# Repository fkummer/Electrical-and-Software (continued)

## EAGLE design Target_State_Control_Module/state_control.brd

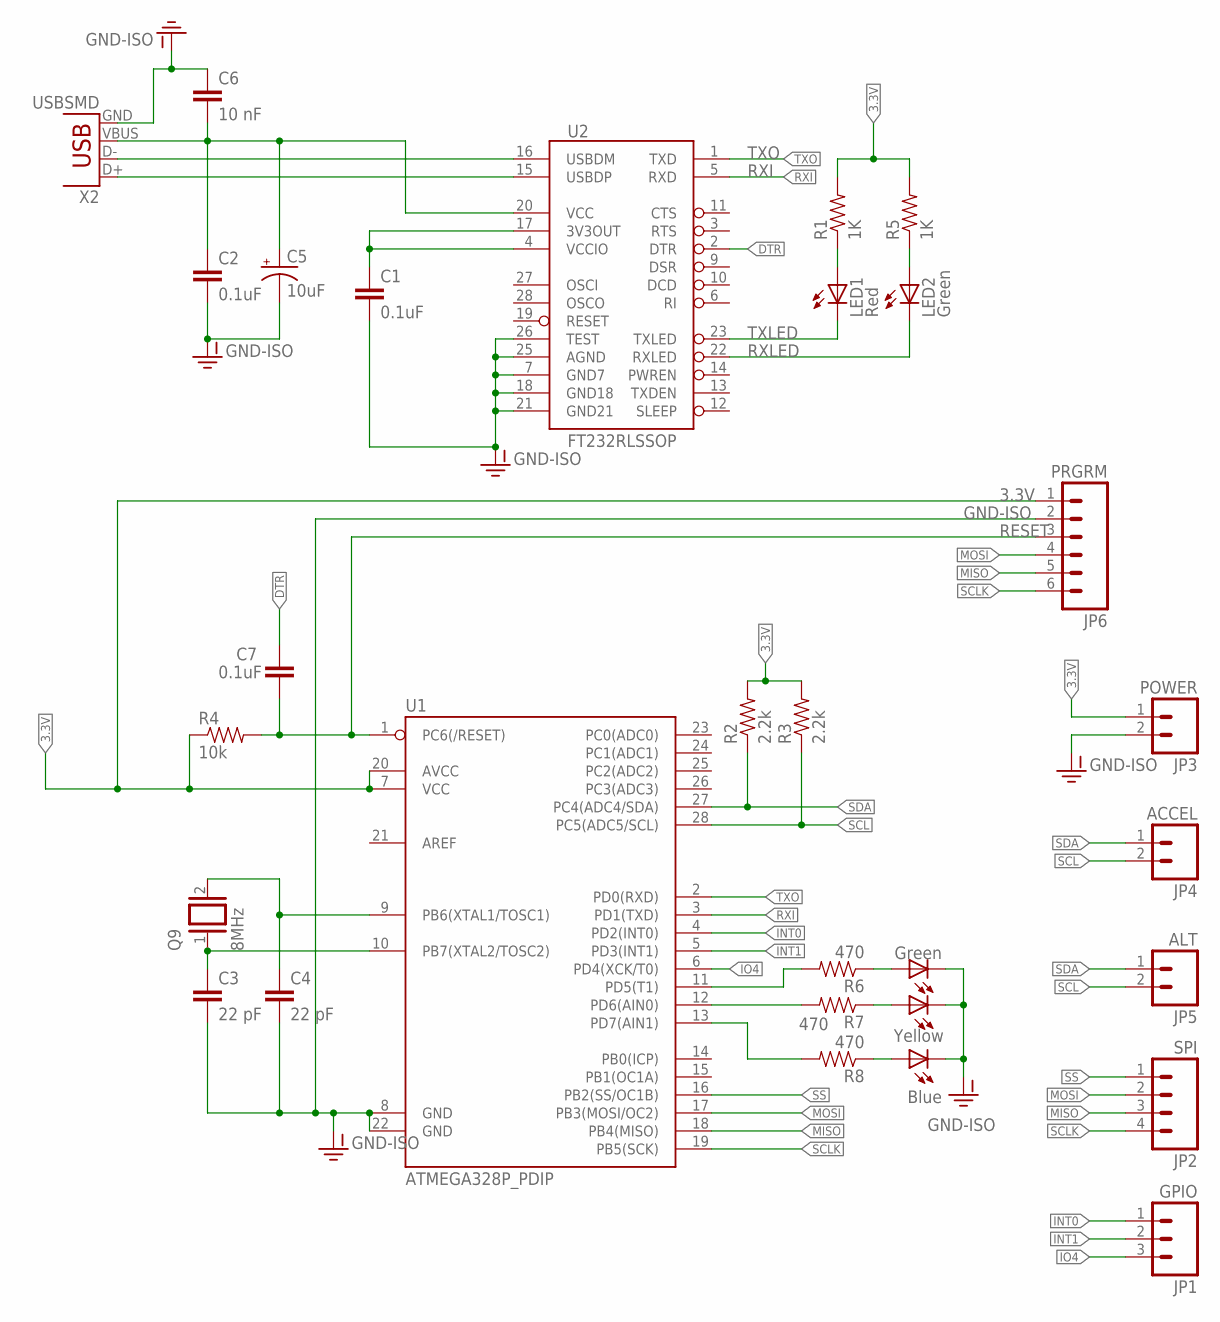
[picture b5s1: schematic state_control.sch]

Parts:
C1, C2, C7: 0.1uF; CAP-PTH-SMALL
C3, C4: 22 pF; CAP-PTH-SMALL
C5: 10uF; CPOL-RADIAL-10UF-25V
C6: 10 nF; CAP-PTH-SMALL
JP1: GPIO; 1X03
JP2: SPI; 1X04
JP3: POWER; 1X02
JP4: ACCEL; 1X02
JP5: ALT; 1X02
JP6: PRGRM; 1X06
LED1: Red; LED5MM
LED2, LED3: Green; LED5MM
LED4: Yellow; LED5MM
LED5: Blue; LED5MM
Q9: 8MHz; QS
R1, R5: 1K; 1206
R2, R3: 2.2k; 1206
R4: 10k; 1206
R6, R7, R8: 470; 1206
U1: ATMEGA328P_PDIP; DIL28-3
U2: FT232RLSSOP; SSOP28DB
X2: USBSMD; USB-MINIB

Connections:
3.3V: JP3.1, JP6.1, R1.2, R2.2, R3.2, R4.1, R5.2, U1.7 (VCC), U1.20 (AVCC)
DTR: C7.1, U2.2 (DTR)
GND-ISO: C1.2, C2.2, C3.2, C4.2, C5.2 (-), C6.1, JP3.2, JP6.2, LED3.K (C), LED4.K (C), LED5.K (C), U1.8 (GND), U1.22 (GND), U2.7 (GND7), U2.18 (GND18), U2.21 (GND21), U2.25 (AGND), U2.26 (TEST), X2.GND
INT0: JP1.1, U1.4 (PD2(INT0))
INT1: JP1.2, U1.5 (PD3(INT1))
IO4: JP1.3, U1.6 (PD4(XCK/T0))
MISO: JP2.3, JP6.5, U1.18 (PB4(MISO))
MOSI: JP2.2, JP6.4, U1.17 (PB3(MOSI/OC2))
unnamed: LED1.A, R1.1
unnamed: LED2.A, R5.1
unnamed: C1.1, U2.4 (VCCIO), U2.17 (3V3OUT)
unnamed: R6.2, U1.11 (PD5(T1))
unnamed: R7.2, U1.12 (PD6(AIN0))
unnamed: R8.2, U1.13 (PD7(AIN1))
unnamed: LED3.A, R6.1
unnamed: LED4.A, R7.1
unnamed: LED5.A, R8.1
unnamed: C3.1, Q9.1, U1.10 (PB7(XTAL2/TOSC2))
unnamed: C4.1, Q9.2, U1.9 (PB6(XTAL1/TOSC1))
RESET: C7.2, JP6.3, R4.2, U1.1 (PC6(/RESET))
RXI: U1.3 (PD1(TXD)), U2.5 (RXD)
RXLED: LED2.K (C), U2.22 (RXLED)
SCL: JP4.2, JP5.2, R3.1, U1.28 (PC5(ADC5/SCL))
SCLK: JP2.4, JP6.6, U1.19 (PB5(SCK))
SDA: JP4.1, JP5.1, R2.1, U1.27 (PC4(ADC4/SDA))
SS: JP2.1, U1.16 (PB2(SS/OC1B))
TXLED: LED1.K (C), U2.23 (TXLED)
TXO: U1.2 (PD0(RXD)), U2.1 (TXD)
USB_D+: U2.15 (USBDP), X2.D+
USB_D-: U2.16 (USBDM), X2.D-
VBUS: C2.1, C5.1 (+), C6.2, U2.20 (VCC), X2.VBUS

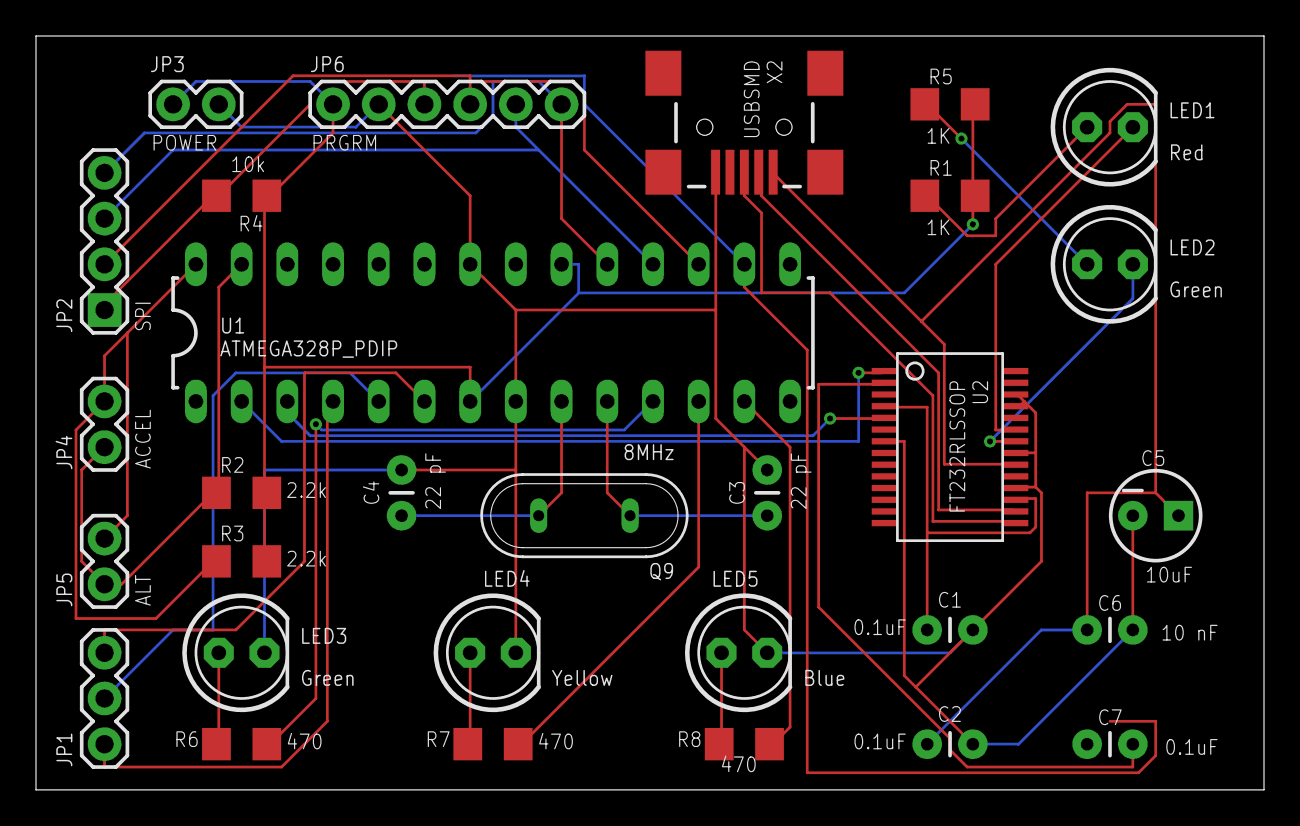
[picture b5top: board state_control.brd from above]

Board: 2 copper layers, 68.2 x 41.9 mm, 30 parts (0 on the bottom side), 31 nets.

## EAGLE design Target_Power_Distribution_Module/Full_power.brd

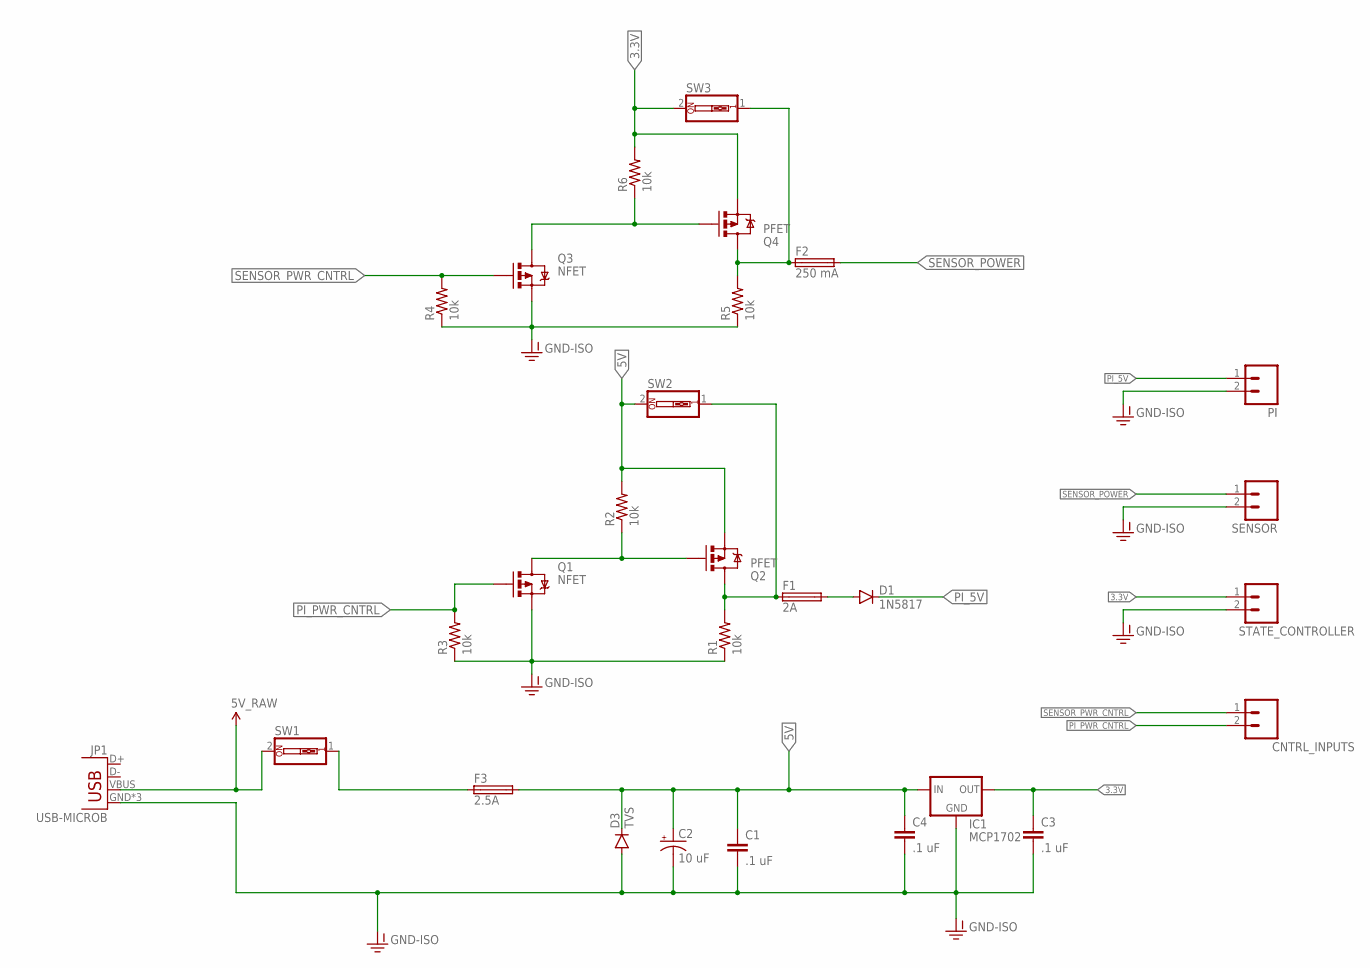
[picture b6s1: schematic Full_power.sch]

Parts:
C1, C3, C4: .1 uF; CAP-PTH-SMALL
C2: 10 uF; CPOL-RADIAL-10UF-25V
CNTRL_INPUTS: M02PTH; 1X02
D1: 1N5817; DIODE-1N4001
D3: TVS; DIODE-1N4001
F1: 2A; PICOFUSE
F2: 250 mA; PICOFUSE
F3: 2.5A; PICOFUSE
IC1: MCP1702; TO92
JP1: USB-MICROB
PI: M02PTH; 1X02
Q1, Q3: NFET; TO220V
Q2, Q4: PFET; TO220V
R1, R2, R3, R4, R5, R6: 10k; R1206
SENSOR: M02PTH; 1X02
STATE_CONTROLLER: M02PTH; 1X02
SW1, SW2, SW3: SW_DIP-1; EDG-01

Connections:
3.3V: C3.1, IC1.3 (OUT), Q4.3 (S), R6.2, STATE_CONTROLLER.1, SW3.2
5V: C1.1, C2.1 (+), C4.1, D3.C, F3.2, IC1.2 (IN), Q2.3 (S), R2.2, SW2.2
5V_RAW: JP1.VBUS, SW1.2
5V_SWITCH: F3.1, SW1.1
GND-ISO: C1.2, C2.2 (-), C3.2, C4.2, D3.A, IC1.1 (GND), JP1.GND, JP1.MT1 (GND), JP1.MT2 (GND), PI.2, Q1.3 (S), Q3.3 (S), R1.1, R3.1, R4.1, R5.1, SENSOR.2, STATE_CONTROLLER.2
unnamed: Q3.2 (D), Q4.1 (G), R6.1
unnamed: Q1.2 (D), Q2.1 (G), R2.1
unnamed: F1.1, Q2.2 (D), R1.2, SW2.1
unnamed: D1.A, F1.2
unnamed: F2.1, Q4.2 (D), R5.2, SW3.1
PI_5V: D1.C, PI.1
PI_PWR_CNTRL: CNTRL_INPUTS.2, Q1.1 (G), R3.2
SENSOR_POWER: F2.2, SENSOR.1
SENSOR_PWR_CNTRL: CNTRL_INPUTS.1, Q3.1 (G), R4.2

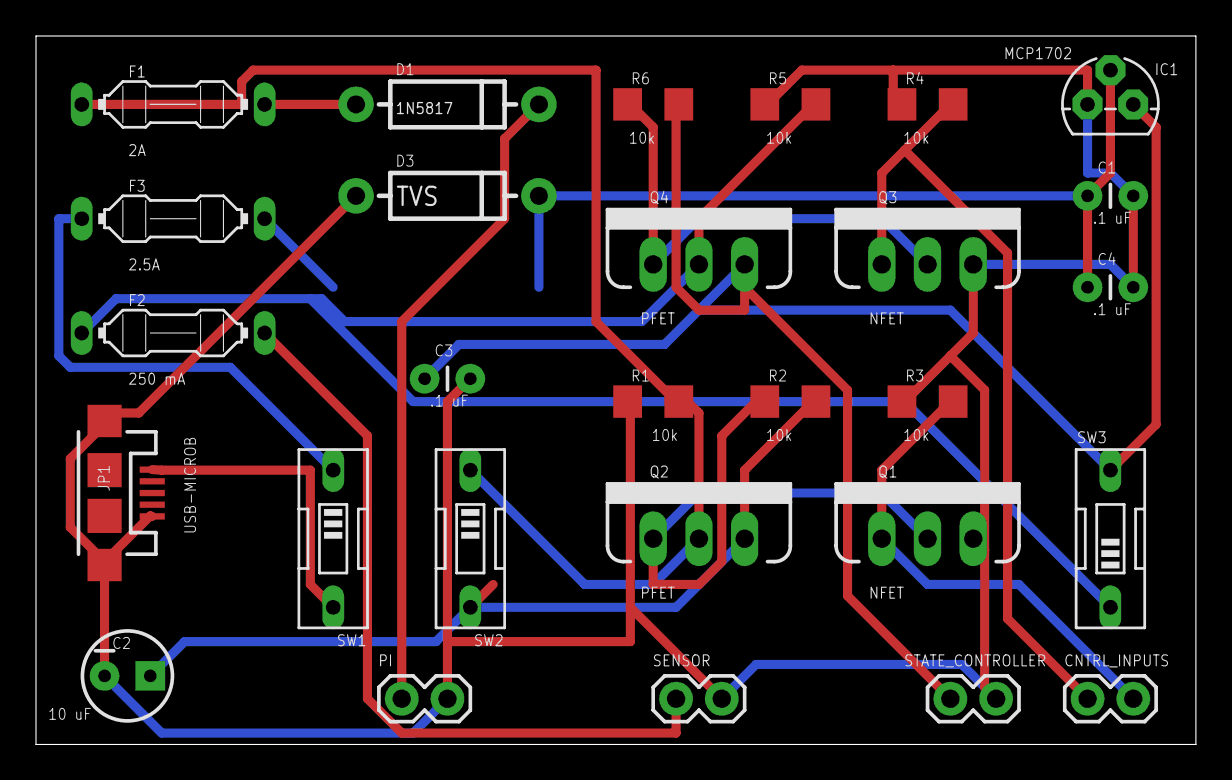
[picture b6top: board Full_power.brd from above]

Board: 2 copper layers, 64.4 x 39.4 mm, 28 parts (0 on the bottom side), 14 nets.

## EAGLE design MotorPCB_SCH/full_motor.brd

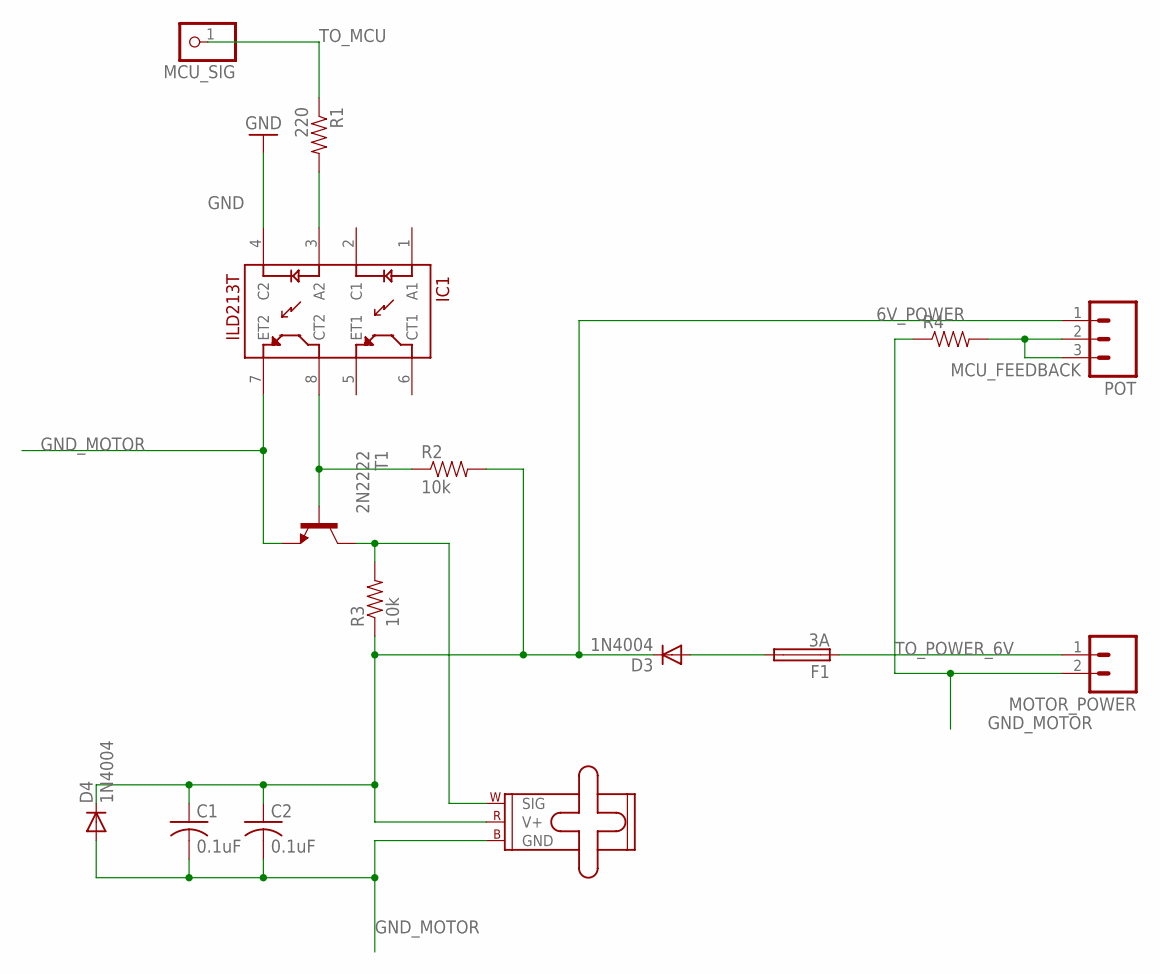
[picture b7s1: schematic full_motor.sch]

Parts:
C1, C2: 0.1uF; C025-024X044
D3, D4: 1N4004; DO41-10
F1: 3A; TE5
IC1: ILD213T; SO08
MCU_SIG: PINHD-1X1; 1X01
MOTOR_POWER: M02PTH; 1X02
POT: M03PTH; 1X03
R1: 220; AXIAL-0.3EZ
R2, R3: 10k; AXIAL-0.3EZ
R4: RESISTOREZ; AXIAL-0.3EZ
SERVO: SMALL_SERVO; 1X03
T1: 2N2222; TO92-EBC-OVAL

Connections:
6V_POWER: C1.1, C2.1, D3.C, D4.C, POT.1, R2.P$2 (2), R3.P$1 (1), SERVO.2 (V+)
GND: IC1.4 (C2)
GND_MOTOR: C1.2, C2.2, D4.A, IC1.7 (ET2), MOTOR_POWER.2, R4.P$1 (1), SERVO.3 (GND), T1.E
MCU_FEEDBACK: POT.2, POT.3, R4.P$2 (2)
unnamed: IC1.3 (A2), R1.P$2 (2)
unnamed: IC1.8 (CT2), R2.P$1 (1), T1.B
unnamed: D3.A, F1.2
unnamed: R3.P$2 (2), SERVO.1 (SIG), T1.C
TO_MCU: MCU_SIG.1, R1.P$1 (1)
TO_POWER_6V: F1.1, MOTOR_POWER.1

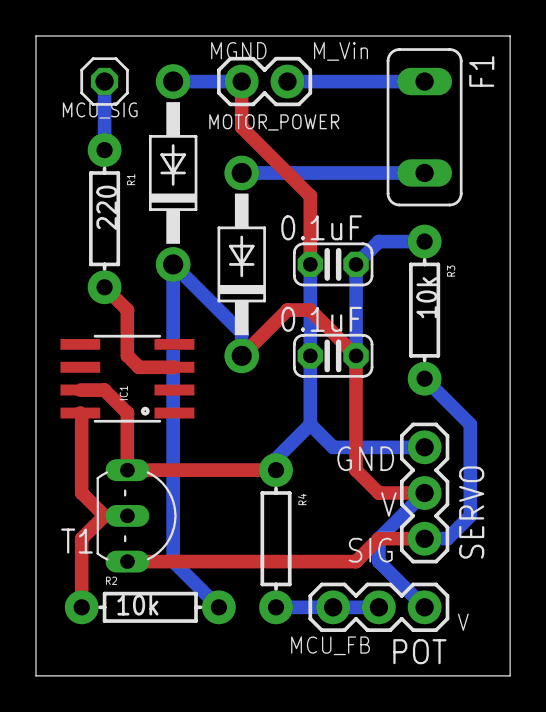
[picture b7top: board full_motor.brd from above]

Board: 2 copper layers, 26.3 x 35.5 mm, 15 parts (0 on the bottom side), 9 nets.

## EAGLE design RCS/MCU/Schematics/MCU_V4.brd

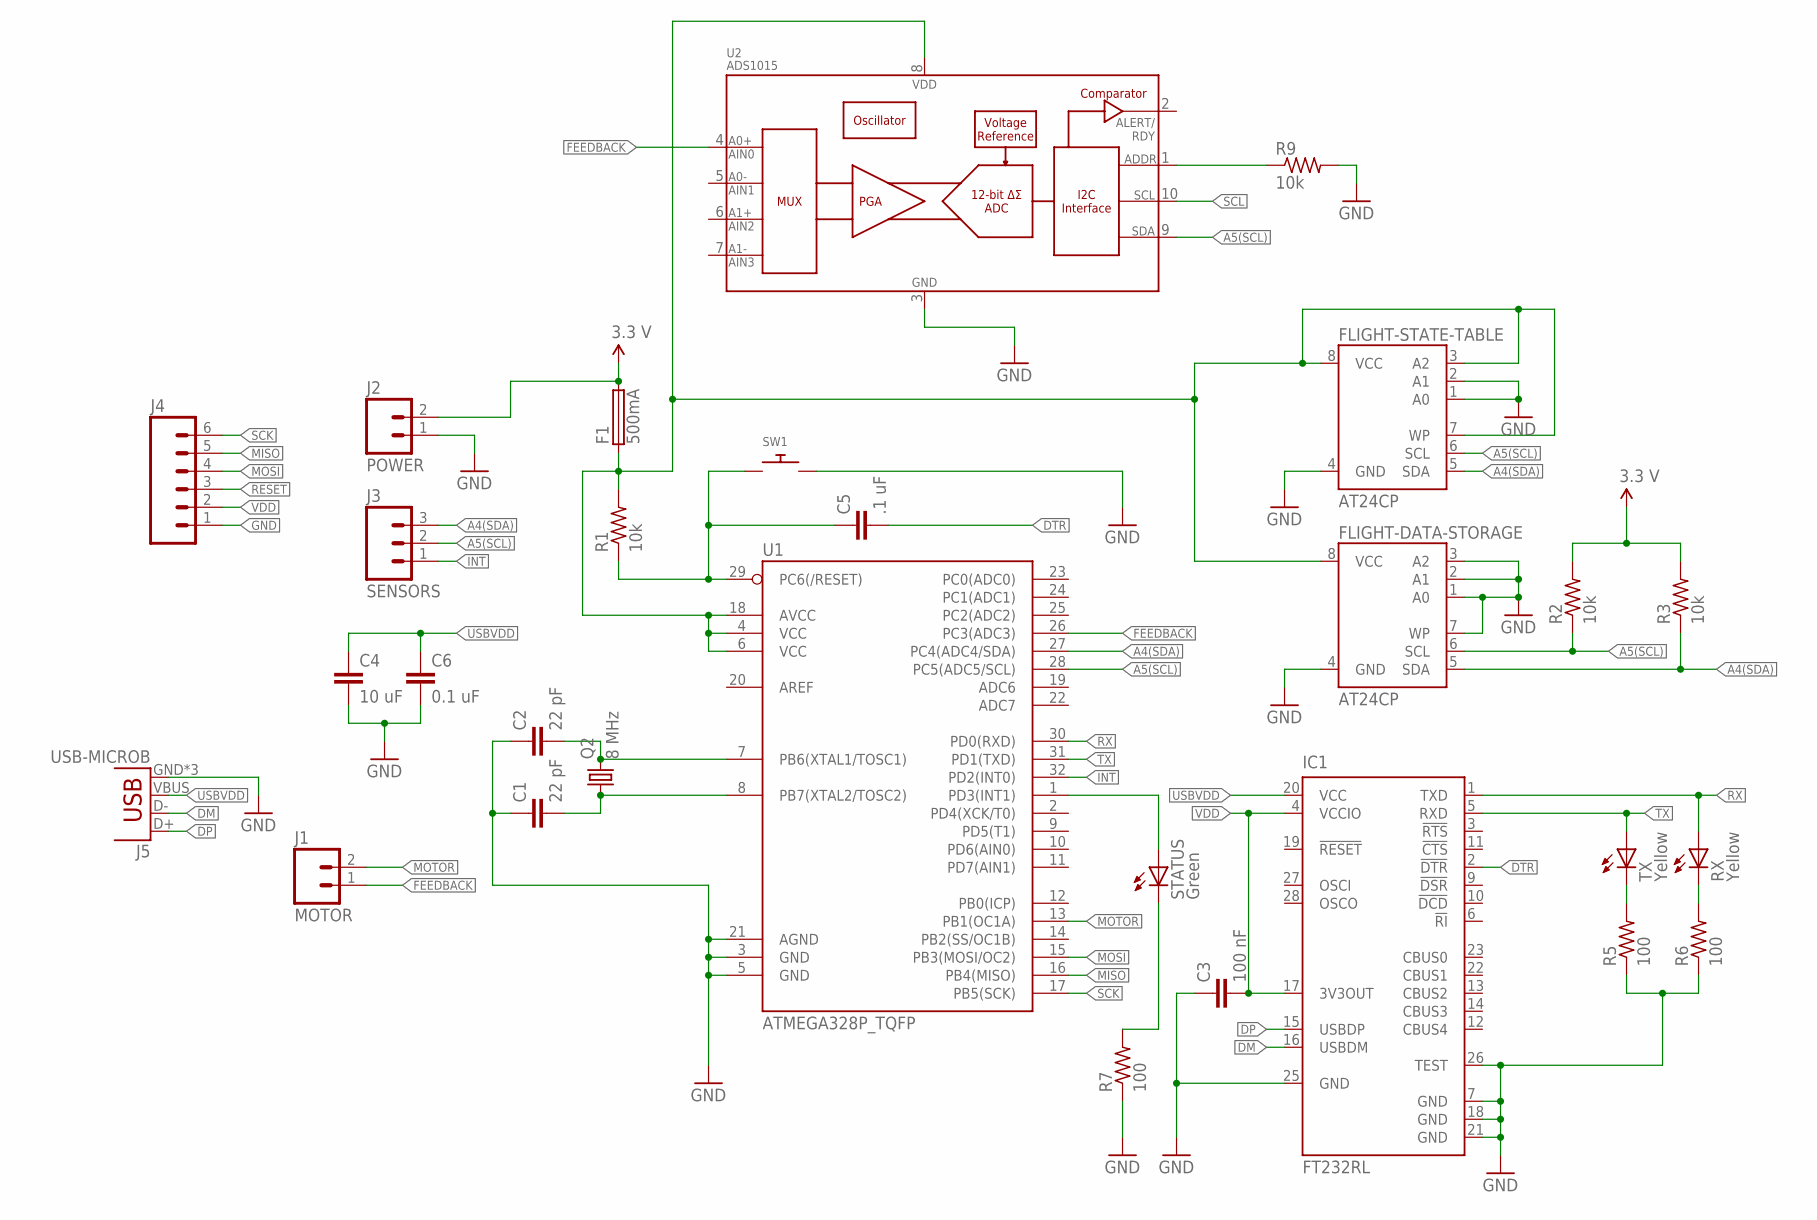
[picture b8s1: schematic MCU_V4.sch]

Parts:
C1, C2: 22 pF; C1206
C3: 100 nF; C1206
C4: 10 uF; C1206
C5: .1 uF; C1206
C6: 0.1 uF; C1206
F1: 500mA; PICOFUSE
FLIGHT-DATA-STORAGE: AT24CP; DIL08
FLIGHT-STATE-TABLE: AT24CP; DIL08
IC1: FT232RL; SSOP28
J1: MOTOR; 1X02_LOCK
J2: POWER; 1X02_LOCK
J3: SENSORS; 1X03_LOCK
J4: M06LOCK; 1X06_LOCK
J5: USB-MICROB
Q2: 8 MHz; HC49/S
R1, R2, R3, R9: 10k; R1206
R5, R6, R7: 100; R1206
RX: Yellow; CHIPLED_1206
STATUS: Green; CHIPLED_1206
SW1: SWITCH_PUSHBUTTONSOFTTOUCHSMD_SJ; PUSHBUTTON_SMD_SJ
TX: Yellow; CHIPLED_1206
U1: ATMEGA328P_TQFP; TQFP32-08
U2: ADS1015; MSOP10

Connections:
A4(SDA): FLIGHT-DATA-STORAGE.5 (SDA), FLIGHT-STATE-TABLE.5 (SDA), J3.3, R3.1, R9.1, U1.27 (PC4(ADC4/SDA)), U2.1 (ADDR)
A5(SCL): FLIGHT-DATA-STORAGE.6 (SCL), FLIGHT-STATE-TABLE.6 (SCL), J3.2, R2.1, U1.28 (PC5(ADC5/SCL)), U2.9 (SDA)
DM: IC1.16 (USBDM), J5.D-
DP: IC1.15 (USBDP), J5.D+
DTR: C5.2, IC1.2 (!DTR)
FEEDBACK: J1.1, U1.26 (PC3(ADC3)), U2.4 (AIN0)
GND: C1.1, C2.1, C3.1, C4.2, C6.2, FLIGHT-DATA-STORAGE.1 (A0), FLIGHT-DATA-STORAGE.2 (A1), FLIGHT-DATA-STORAGE.3 (A2), FLIGHT-DATA-STORAGE.4 (GND), FLIGHT-DATA-STORAGE.7 (WP), FLIGHT-STATE-TABLE.1 (A0), FLIGHT-STATE-TABLE.2 (A1), FLIGHT-STATE-TABLE.4 (GND), IC1.7 (GND), IC1.18 (GND), IC1.21 (GND), IC1.25 (GND), IC1.26 (TEST), J2.1, J4.1, J5.GND, J5.MT1 (GND), J5.MT2 (GND), R5.1, R6.1, R7.1, R9.2, SW1.P$2, U1.3 (GND), U1.5 (GND), U1.21 (AGND), U2.3 (VSS)
INT: J3.1, U1.32 (PD2(INT0))
MISO: J4.5, U1.16 (PB4(MISO))
MOSI: J4.4, U1.15 (PB3(MOSI/OC2))
MOTOR: J1.2, U1.13 (PB1(OC1A))
unnamed: F1.1, FLIGHT-DATA-STORAGE.8 (VCC), FLIGHT-STATE-TABLE.3 (A2), FLIGHT-STATE-TABLE.7 (WP), FLIGHT-STATE-TABLE.8 (VCC), R1.2, U1.4 (VCC), U1.6 (VCC), U1.18 (AVCC), U2.8 (VDD)
unnamed: C2.2, Q2.2, U1.7 (PB6(XTAL1/TOSC1))
unnamed: C1.2, Q2.1, U1.8 (PB7(XTAL2/TOSC2))
unnamed: STATUS.A, U1.1 (PD3(INT1))
unnamed: R7.2, STATUS.C
unnamed: R5.2, TX.C
unnamed: R6.2, RX.C
RESET: C5.1, J4.3, R1.1, SW1.P$1, U1.29 (PC6(/RESET))
RX: IC1.1 (TXD), RX.A, U1.30 (PD0(RXD))
SCK: J4.6, U1.17 (PB5(SCK))
SCL: U2.10 (SCL)
TX: IC1.5 (RXD), TX.A, U1.31 (PD1(TXD))
USBVDD: C4.1, C6.1, IC1.20 (VCC), J5.VBUS
VDD: C3.2, F1.2, IC1.4 (VCCIO), IC1.17 (3V3OUT), J2.2, J4.2, R2.2, R3.2

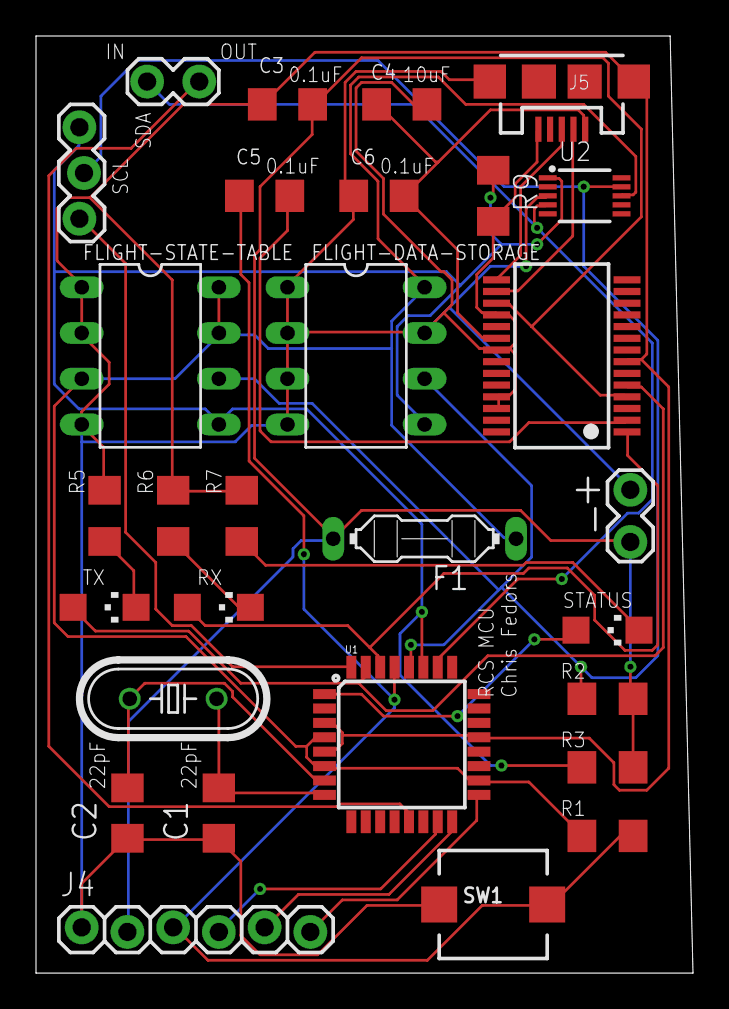
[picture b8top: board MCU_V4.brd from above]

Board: 2 copper layers, 36.5 x 52.1 mm, 29 parts (0 on the bottom side), 24 nets.

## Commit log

2016-09-27 Added training directory
2016-09-28 Added Liam Patterson's training 555 timer schematic
2016-10-02 Create Joshi_Sanskriti
2016-10-02 Repaired original design
2016-10-08 Hopefully made the schematic a little easier to read.
2016-10-13 laasya's training project
    sorry this is so late :(
2016-10-14 Add overvoltage, overcurrent, decoupling schematic
    Added schematic for overvoltage, overcurrent, and decoupling. Use a
    fuse, PTC, and TVS for protection. Two decoupling capacitors
2016-10-14 Added battery and battery connector
2016-10-16 updated training project
    thanks
2016-10-16 Additional modifications to repaired design
    Changes were made based on comments
2016-10-18 Revised schematic to be neat and work.
2016-10-19 ERC ran without error, fixed threshold pin.
2016-10-19 Schematic for sensor test rig
    First rev of sensor test rig, uses sparkfun breakout board and EEPROM
2016-10-19 Cleaning up directory
2016-10-19 Added basic schematic and tenative parts list
2016-10-30 Test text
2016-11-04 Updated Schematic
2016-11-04 Moved updated schematic to folder
2016-11-08 Updated V3 Schematic
2016-11-08 Added Resistors in series with LEDs
2016-11-08 Create TD Sensor Schematic
    I did my best, it's a little messy though.
2016-11-10 Rename TD Sensor Schematic to TDSensorSchematic.sch
2016-11-11 Added voltage regulator that assumes 5V battery pack
2016-11-12 Add files via upload
    fixed the Schematic
2016-11-12 The schematic for the Accelerometer/Gyroscope
2016-11-16 Deleted MCU_V4, since it was not the most recent update
2016-11-18 Added GPIO LED and Capacitors on USB line
2016-11-18 Started working on PCB
2016-11-18 Updated/New Schematics
    I don't think this updated when I did it on tuesday
2016-11-20 Moving to using 5V USB pack
2016-11-20 Fixed connection with resistor
2016-11-20 Added label to power and fixed resistor connection
2016-11-20 Got rid of old poorly named directory
2016-11-20 Added power control
2016-11-20 Created full power schematic
2016-11-20 Added backup switches in case power control fails
2016-11-30 fixed ERC warnings
2016-11-30 labeled VCC 3.3V
2016-11-30 Completed PCB layout
2016-11-30 Started on brd
2016-12-04 Initial .brd done for power
2016-12-04 Fixed labels
2016-12-05 Combination of the two sensors
2016-12-05 Updated the final schematic
    forgot to connect CSB to ground for the altimeter
2016-12-06 Add files
    Alright I figured out how to do it.
2016-12-06 Board and BOM
2016-12-06 BOM added
2016-12-06 PCB for motor
2016-12-09 PCB for sensor module
    forgot to upload, sorry!!!
2016-12-12 Added labels
2016-12-14 Fixed up the schematics and PCBs for power dist
2016-12-14 A bit more
2016-12-16 Schematic for PCB added
2016-12-17 schem
2016-12-17 Added PCB
2016-12-17 final_sensors_board
2016-12-18 Began Full
2016-12-18 Rename TDSensorBoard.brd to SensorModule.brd
2016-12-18 fixed label sizes, renamed files
2016-12-23 full sch
2016-12-23 added GPIO
2016-12-23 gpio
2016-12-23 Trace widths
2016-12-23 fix outline
2016-12-23 removed to prevent conflict
2017-01-13 Slightly updated schematic
2017-01-14 Updated schematic and Started Coding
    Added SPI support on schematic
2017-01-14 Code for the altimeter simulator and master
2017-01-14 Some schematic updates
2017-01-14 Began integrating SCM with altimeter
2017-01-14 Added power indicator
2017-01-16 Updated Master for Altimeter
    this the is updated test with the code to adjust the altimeter readings
2017-01-16 Updated INTEV Schematic
2017-01-16 Added Accel code
2017-01-17 Accelerometer and Gyro code
    this is the simulation and the master code for MPU9250 sensor
2017-01-17 Added comments
2017-01-17 Updated code and combined sensors
2017-01-17 Some clean up of git
2017-01-18 More INTEV board updates
2017-01-18 first draft of target detection
2017-01-18 target detection that uses functions. version 2
2017-01-19 Updated schematic and board
2017-01-19 updated schematic and board
    used a different eagle schematic for the mpu-9250 to allow help resolve
    clearance issues
2017-01-19 Updated board file
    Fixed clearance
2017-01-19 Some schematic updates, spi test is working
2017-01-19 Updated SCM to disassociate SS and RESET
2017-01-19 Updated MCU
    Added adc, SPI connection, mini USB
2017-01-19 Cleaned sensor on full schem
2017-01-19 final pcb combined power
2017-01-19 Switched to QFP
2017-01-19 schematic for entire RCS
2017-01-19 Schem touch up
2017-01-19 Replaced capacitors with 1206
2017-01-19 Updates to full schematic
    not done, still going over connections
2017-01-20 Updated diode part
2017-01-20 updated parts
2017-01-20 fixed parts
2017-01-20 More MCU Updates
2017-01-20 Replaced transistors with SMD part
2017-01-20 test
2017-01-20 changed header
2017-01-20 Changed VDD to LOGIC_VDD
2017-01-20 Schematic should be ready, starting board
2017-01-20 change
2017-01-20 one ic switched
2017-01-20 changed diode
2017-01-20 mpu9250 stuff
2017-01-20 hopefully it works
2017-01-20 board
2017-01-21 started
2017-01-21 Some schematic adjustments and board progress
2017-01-21 Made MCU section
2017-01-21 power
2017-01-21 Small Update to board
2017-01-21 yayyyyy
2017-01-21 Board possibly done, need more checking
2017-01-21 some small board touch up
2017-01-21 SMASHED
2017-01-21 Done?
2017-01-21 cool beans
2017-01-22 Fixed silkscreen on RCS
2017-01-22 ordering tds
2017-01-22 Updated Full BOM
2017-01-22 Fixed BOM
2017-01-24 Completed TDS BOM and ordering
2017-01-26 updated with altitude adjustment
    under comment : adjust the altitude values by val meters
2017-01-27 This includes the adjustment
    under comment “adjust the altitude values by val meters”
2017-01-27 update to altimeter simulation
    this includes the array of import values
2017-01-29 Changed SPI code to send 16 bits
2017-01-29 Added python spi code
2017-01-31 Adjusting altitude
2017-01-31 Added GPIO pin to arduino side
2017-01-31 Added GPIO support to pi side
2017-01-31 altimeter code
2017-01-31 launch detection
2017-01-31 started debugging ascent altimeter based photo taking
2017-02-01 Working towards fullscale
2017-02-03 Fixing TDS code
2017-02-03 Simulator tune up and transition TDS to state machine
2017-02-04 Almost ready for full-scale
2017-02-04 Ready for fullscale
2017-02-04 latest code
2017-02-05 not sure what changed in the bom
2017-02-05 changes to schematic
    board is not ready yet
2017-02-05 mpu changes
2017-02-05 new bom
2017-02-05 Updated BOM
2017-02-05 Added a link for mpu9250 breakout
2017-02-05 changes?
2017-02-05 lock
2017-02-05 new board
2017-02-05 bom update
2017-02-05 Got rid of hubbytronics link
2017-02-05 Full TDS rev2
2017-02-05 Last additions to the BOM
2017-02-06 added 1 servo
    just to be safe
2017-02-06 New TDS rev
2017-02-06 New RCS Rev
2017-02-18 TDS initial commit
2017-02-18 targetDetectionWebcam contains the final code for taking and processing the pictures
2017-02-20 Parallelized process
2017-03-08 Added Code back to MCU branch
2017-03-08 Added test code
2017-03-12 Test Code added
2017-03-12 add debouncing
2017-03-12 Added new acclerometer code to RCS_TEST
2017-03-13 small edits
2017-03-19 updates to spi
2017-03-19 updates spi on arduino side
2017-03-24 Fixed fatal flaws in RCS code
2017-03-26 adjusted color values
2017-04-03 more processing
2017-04-04 competition
2017-04-17 555
    0603
2017-04-23 post comp
2017-04-30 flasher with components on 2 sides
2017-05-07 board added
